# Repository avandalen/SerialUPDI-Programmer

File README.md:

# SerialUPDI-Programmer
Burning a bootloader into the ATtiny3217 with the SerialUPDI Programmer.

The files are Eagle files

You can read the entire article here:
https://avdweb.nl/arduino/attiny3217/bootloader-attiny3217

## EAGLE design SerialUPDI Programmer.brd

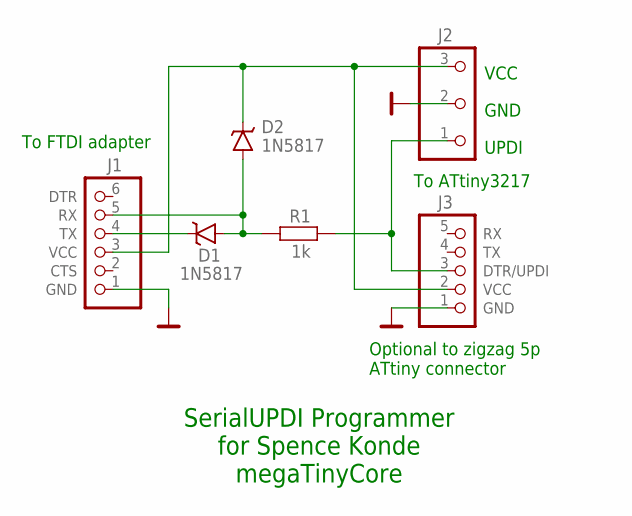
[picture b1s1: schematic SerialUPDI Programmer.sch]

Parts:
D1, D2: 1N5817; SOD523
J1: 6P; 1X06
J2: nc; 1X03
J3: nc; FTDI-UPDI-5P
R1: 1k; 0603

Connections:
5V: D2.C, J1.3 (VCC), J2.3, J3.2 (VCC)
GND: J1.1 (GND), J2.2, J3.1 (GND)
unnamed: D1.A, D2.A, J1.5 (RX), R1.1
unnamed: D1.C, J1.4 (TX)
UPDI: J2.1, J3.3 (DTR/UPDI), R1.2

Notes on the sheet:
SerialUPDI Programmer for Spence Konde megaTinyCore
VCC
GND
UPDI
To ATtiny3217
To FTDI adapter
Optional to zigzag 5p ATtiny connector

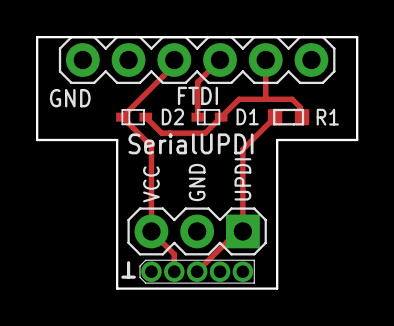
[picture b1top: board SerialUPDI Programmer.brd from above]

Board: 2 copper layers, 17.8 x 14.0 mm, 6 parts (0 on the bottom side), 5 nets.

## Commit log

2024-06-30 Create vcxvxc
